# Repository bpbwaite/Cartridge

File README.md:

# Cartridge

Tools for creating a physical game library.

---

## Description

Cartridge lets you launch PC games with NFC tags - without any software running on your computer.

---

|  |  |
|------------------------------------|------------------------------------|

---

### Features

+ Guided setup
    + Automatically generates your game list without any sign-ins
    + Automatically generates a printable library PDF, to cut and paste on your 3D printed Cartridges
    + Semi-automated NFC tag provisioning
    + Prints and writes only newly acquired game tags
+ Configurable Reader
    + Launch any game or executable file by placing a Cartridge on the Reader
    + Send a hotkey combination when launching SteamVR games (e.g. to launch WiGig software or power on bay-stations)
    + Option to close Steam games when a new game is launched via Cartridge
    + Option to launch a random game with a specific Cartridge
    + Stylish indicator LEDs

+ ***NOTE:*** Cartridge is still in development. It only works on Windows 10/11. Library image generation is limited to Steam games at the moment.
    + Upcoming features: Sound effects, Linux support (with some additional setup), optional WiFi module?

---

### Why?

Because it's super cool, and having a physical representation of your library makes it fun and easy to share.

## Building From Source

*Requirements:* [uv](https://docs.astral.sh/uv/), Python 3.11.9 or later, PlatformIO
```powershell
cd cartridge-setup
uv run python src/main.py
pio run
pio run -t upload
```
Press the button on the Teensy if/when the uploader asks for it.

---

---

## Assembly

### Hardware & Materials

You will need:

+ 1x Teensy 4.0
+ 1x PN532 NFC Module
+ 1x Micro USB Cable (with functional D+/D- wires)
+ 1x FR4 Protoboard -OR- a populated PCB
+ 1x DIP Switch (3 switches, 6 pin)
+ 7x Self-tapping 2.5mm Screws
+ Neopixel Strip (3 LEDs long)
+ 3x Mini Rubber Feet
+ NTAG215 Stickers (x however many games you have)
+ 6mm by 2mm magnets (2x however many games you have)
+ Super Glue
+ Photo paper
+ Rubber cement
+ 3D Printer filament

(todo assembly instructions)

## Demo

https://www.youtube.com/watch?v=b9ThTMVmSbA

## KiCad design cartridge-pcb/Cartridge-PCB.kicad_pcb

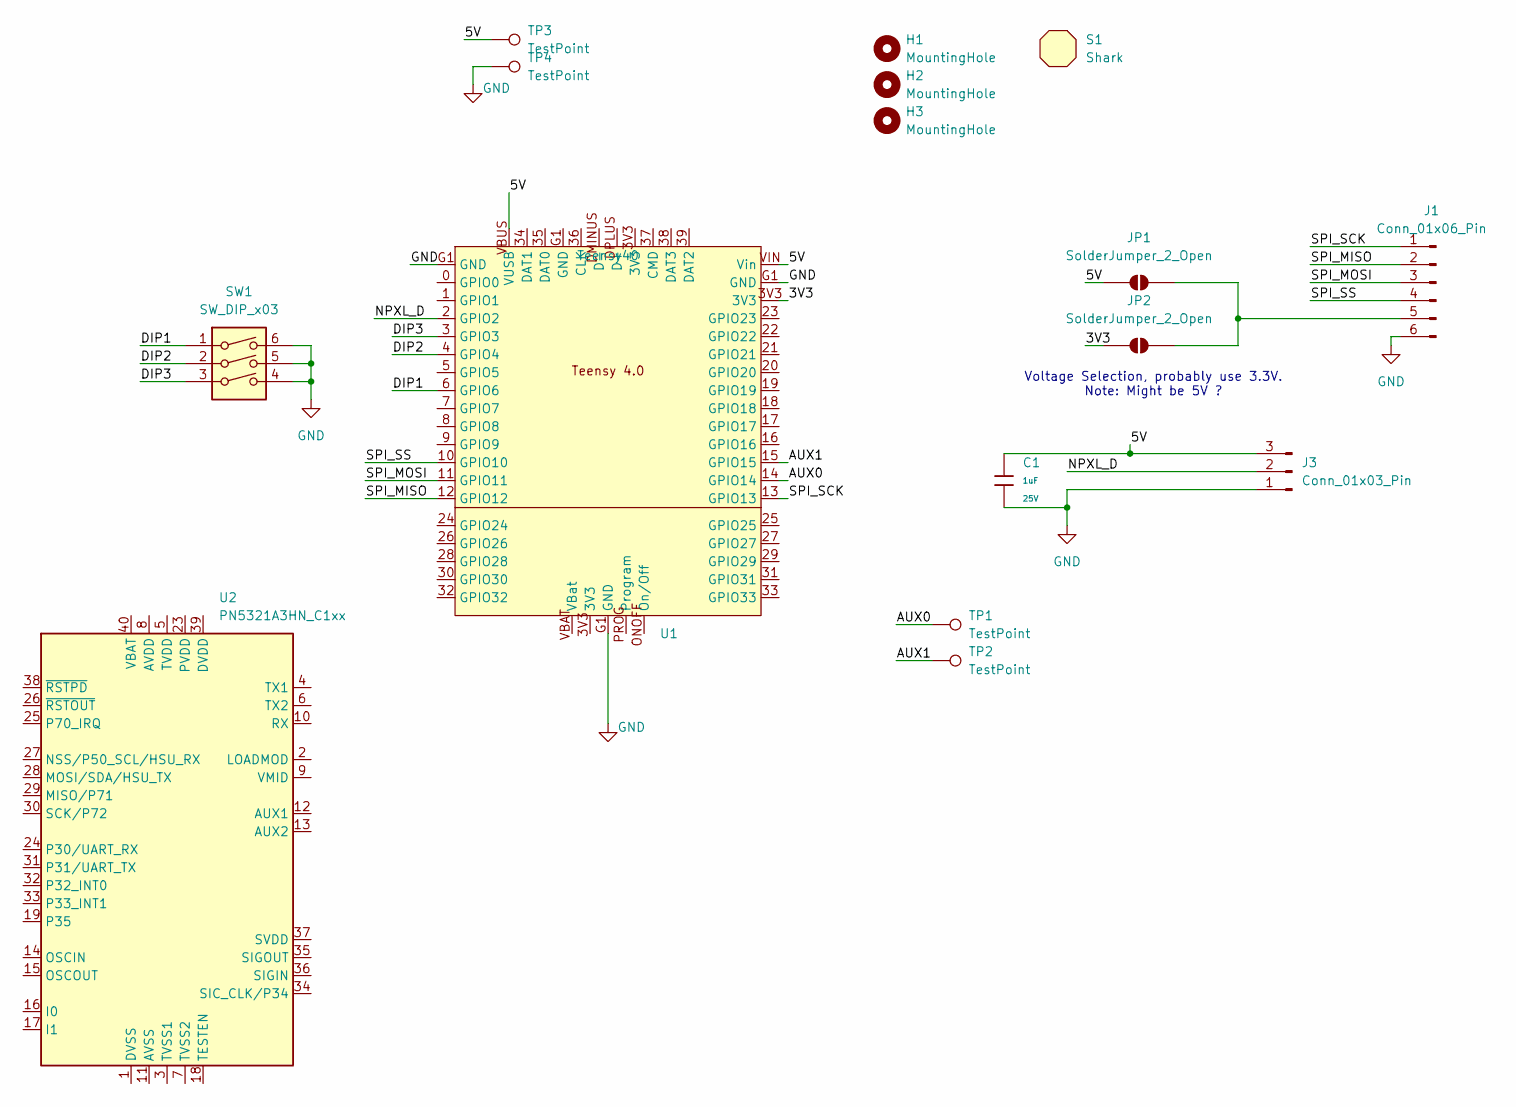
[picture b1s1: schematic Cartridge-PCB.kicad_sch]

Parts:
C1: 1uF; C_0603_1608Metric_Pad1.08x0.95mm; Voltage Rated 25V; Tolerance ±10%; Part CL10A105KB8NNNC; LCSC C15849
H1, H2, H3: MountingHole; MountingHole_2.2mm_M2
J1: Conn_01x06_Pin; PinHeader_1x06_P2.54mm_Horizontal
J3: Conn_01x03_Pin; JST_XH_B3B-XH-A_1x03_P2.50mm_Vertical
JP1, JP2: SolderJumper_2_Open; SolderJumper-2_P1.3mm_Open_RoundedPad1.0x1.5mm
S1: Shark; Smolhaj_Scale_0.1
SW1: SW_DIP_x03; SW_DIP_SPSTx03_Slide_9.78x9.8mm_W7.62mm_P2.54mm
TP1, TP2: TestPoint; TestPoint_Pad_D1.5mm
TP3, TP4: TestPoint; TestPoint_Pad_1.5x1.5mm
U1: Teensy40; Teensy_4.0
U2: PN5321A3HN_C1xx; HVQFN-40-1EP_6x6mm_P0.5mm_EP4.1x4.1mm

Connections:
/3V3: JP2.1 (A), U1.3V3
/5V: C1.1, J3.3, JP1.1 (A), TP3.1 (1_1), U1.VBUS (VUSB), U1.VIN (Vin)
/AUX0: TP1.1 (1_1), U1.14 (GPIO14)
/AUX1: TP2.1 (1_1), U1.15 (GPIO15)
/DIP1: SW1.1, U1.6 (GPIO6)
/DIP2: SW1.2, U1.4 (GPIO4)
/DIP3: SW1.3, U1.3 (GPIO3)
/NPXL_D: J3.2, U1.2 (GPIO2)
/SPI_MISO: J1.2, U1.12 (GPIO12)
/SPI_MOSI: J1.3, U1.11 (GPIO11)
/SPI_SCK: J1.1, U1.13 (GPIO13)
/SPI_SS: J1.4, U1.10 (GPIO10)
GND: C1.2, J1.6, J3.1, SW1.4, SW1.5, SW1.6, TP4.1 (1_1), U1.G1 (GND)
unnamed: J1.5, JP1.2 (B), JP2.2 (B)
unnamed: U2.11 (AVSS), U2.41 (AVSS)

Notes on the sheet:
Voltage Selection, probably use 3.3V. Note: Might be 5V ?

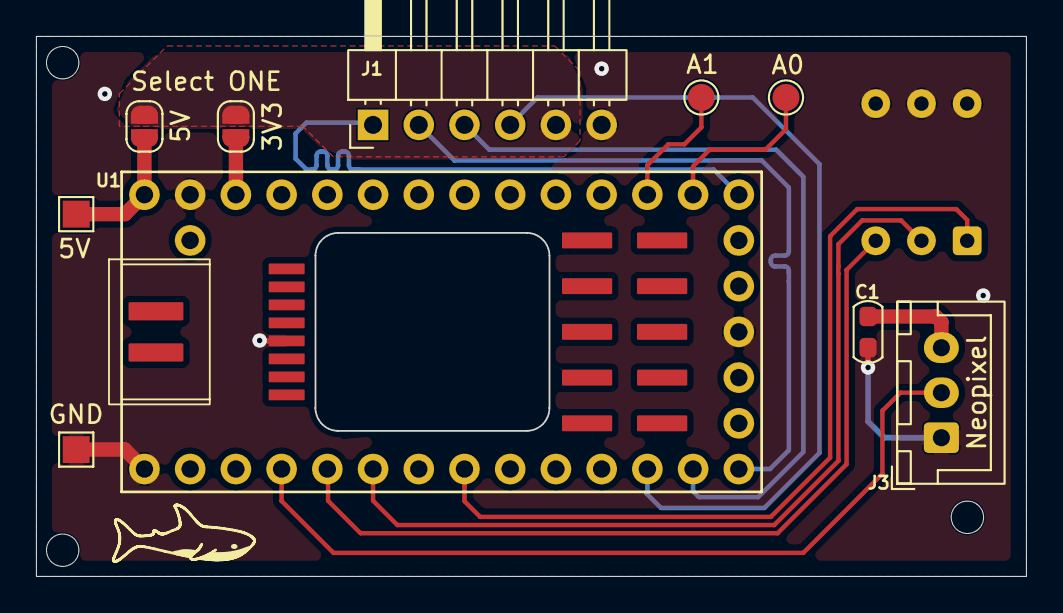
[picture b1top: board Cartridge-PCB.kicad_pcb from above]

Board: 2 copper layers, 55.0 x 30.0 mm, 15 parts (1 on the bottom side), 14 nets.
